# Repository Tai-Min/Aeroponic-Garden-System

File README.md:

# Thingy:53 Aeroponic Garden
2nd place in [Smarter Sustainable World Challenge
with Nordic Semiconductor](https://www.hackster.io/contests/smarter-sustainable-world). For details of the project itself see [Vertical Self Regulating Soilless Farm](https://www.hackster.io/Tai-Min/vertical-self-regulating-soilless-farm-a86d25)

## Physical setup
### The pot
* Print heater_bottom_n.stl and heater_top_n.stl (n = 1, 2, 3, 4) and glue them together. Insert 12V 5050 fan into place
* Print funnel.stl and insert it into heater glued in previous step
* Print num_layers * 4 layer_quarter.stl and glue them together then stack the layers and place them on top of the heater
* Print num_layers nozzle_frame.stl and num_layers * 4 nozzle_single.stl and glue them together then using straight plastic pipe assemble them starting from funnel's center intlet so that each nozzle_frame is on the level of the pot of given layer  
* Print nozzle_frame_end.stl and insert it at the top of previously created piping
* Print top_hat.stl and insert it at the top of vertical pot then insert Thingy:53 into it 
* Create wooden frame as in the pictures below
* Print valve_holder.stl and screw it at the bottom of the wooden quadropod then screw 12V valves into places
* Print num_layers * 4 - 1 of water_nozzle_frame.stl and nozzle_single.stl and glue them together then screw them on wooden structure so that each nozzle faces one pot
* Print 1 water_nozzle_frame_end.stl and single_nozzle.stl and glue them together and screw it on the wooden structure so it faces one pot
* Install LED strips on wooden structure so each pot has it's own light source

### RPi water system
* Print 2 pipe_holder_1.stl and pipe_holder_2.stl and glue them together on the side of both liquid tanks
* Print 2 pump_holder.stl and glue it at the bottom of the tank then screw the 12V pump into it
* Print 2 water_level_holder.stl, place it on the lids of both liquid tanks and then snap an ultrasonic sensor into them
* Screw reed switches into both liquid tanks and corresponding magnets into lids
* On nutrition water tank mount PCBs for EC and pH sensors and place the sensors into the tank itself

### Putting it together
Use flexible piping to connect the pot to water system as in the block diagram below:

## Electronics
Refer to KiCad project in /pi_shield folder for BOM and assembly purposes of the hats.

### The pot
Connect sensors / actuators to Thingy:53 control hat as in the block diagram below:

### RPi water system
Connect sensors / actuators to RPi's control hat as in the block diagram below:

## Attiny85
* Connect some programmer (i.e. ArduinoISP or USBasp) to Attiny85
* In platformio.ini change upload_protocol to your programmer
* You might also want to fine tune PH_MAGIC_NUMBER, TDS_A, TDS_B variables to match your sensor's characteristics
* In PlatformIO menu press "Set Fuses" in "attiny85" configuration, then click "Upload"
* Insert Attiny85 into Farm Overseers's shield

## Farm Overseer setup
* Setup Ubuntu Server 20.04 (i.e via [Raspberry Pi Imager](https://www.raspberrypi.com/software/))

### Enable UART
* Disable serial console
```
sudo systemctl stop serial-getty@ttyS0.service
sudo systemctl disable serial-getty@ttyS0.service
sudo systemctl mask serial-getty@ttyS0.service
```
* Put below into /etc/udev/rules.d/10-local.rules
```
KERNEL=="ttyS0", SYMLINK+="serial0" GROUP="tty" MODE="0660"
KERNEL=="ttyAMA0", SYMLINK+="serial1" GROUP="tty" MODE="0660"
```
* Reload udev rules
```
sudo udevadm control --reload-rules && sudo udevadm trigger
```
* Add user to tty (edit parts in "<>")
```
sudo adduser <USER> tty
```
* Delete below from /boot/firmware/cmdline.txt
```
console=serial0,115200
```
* Add below to /boot/firmware/config.txt
```
dtoverlay=disable-bt
```
### Enable 1-Wire
* Add below to /boot/firmware/config.txt
```
dtoverlay=w1-gpio,gpiopin=4
```

### ROS2
* Install [ROS2 Foxy Base version](https://docs.ros.org/en/foxy/Installation/Ubuntu-Install-Debians.html)
* Clone this repo to your home directory (/home/$USER/TODO)
* Build ROS components:
```bash
cd ~/TODO/ros_workspace && colcon build
```
* Place ROS setups in your .bashrc (edit parts in "<>")
```
source /opt/ros/foxy/setup.bash
source /home/<USER>/TODO/ros_workspace/install/setup.bash

```
### Mosquitto
* Install mosquitto 2.0
```
sudo add-apt-repository -y ppa:mosquitto-dev/mosquitto-ppa
sudo apt install mosquitto
sudo systemctl enable mosquitto
```

### zigbee2mqtt
* Install [zigbee2mqtt](https://www.zigbee2mqtt.io/guide/installation/01_linux.html) and set it to start as a daemon on boot. Use following config (edit parts in "<>"):
```yaml
mqtt:
  base_topic: field
  server: 'mqtt://localhost'

serial:
  port: <YOUR ZIGBEE DONGLE PORT>

advanced:
    network_key: GENERATE

external_converters:
  - fc.js
```

Create file /opt/zigbee2mqtt/data/fc.js and paste following into it:
```js
const fz = require('zigbee-herdsman-converters/converters/fromZigbee');
const tz = require('zigbee-herdsman-converters/converters/toZigbee');
const exposes = require('zigbee-herdsman-converters/lib/exposes');
const reporting = require('zigbee-herdsman-converters/lib/reporting');

const definition = {
    zigbeeModel: ['FC_v0.1'],
    model: 'FC',
    vendor: 'Nordic',
    description: 'Field Controller',
    fromZigbee: [fz.temperature, fz.humidity, fz.pressure, fz.on_off, fz.level_config],
    toZigbee: [tz.on_off, tz.level_config],
    exposes: [],
    configure: async (device, coordinatorEndpoint, logger) => {
        await reporting.bind(device.getEndpoint(16), coordinatorEndpoint, ['msTemperatureMeasurement']);
        await reporting.temperature(device.getEndpoint(16), { min: 30, max: 30, change: 0 });

        await reporting.bind(device.getEndpoint(16), coordinatorEndpoint, ['msPressureMeasurement']);
        await reporting.pressure(device.getEndpoint(16), { min: 30, max: 30, change: 0 });

        await reporting.bind(device.getEndpoint(16), coordinatorEndpoint, ['msRelativeHumidity']);
        await reporting.humidity(device.getEndpoint(16), { min: 30, max: 30, change: 0 });
    },
    endpoint: (device) => {
        return { fan: 10, led1: 11, led2: 12, strat: 13, water_valve: 14, nutri_valve: 15, sensors: 16 };
    },
};

module.exports = definition;
```

### Finishing up
* Reboot the board
```
sudo reboot now
```

## Field controller setup
Open field_controller/ in VSCode with nRF Connect and with Thingy:53 connected via JLink press flash.

## Run Farm Overseer's control algorithms
SSH into the Farm Overseer and run:
```
ros2 launch garden_meta system.launch.py
```

## Pair field controller to Farm Overseer
With Field Controller running cd into scripts/ and run:
```
./pair.sh -t 300
``` 
This will enable pairing for 300 seconds and should pair with the Field Controller.

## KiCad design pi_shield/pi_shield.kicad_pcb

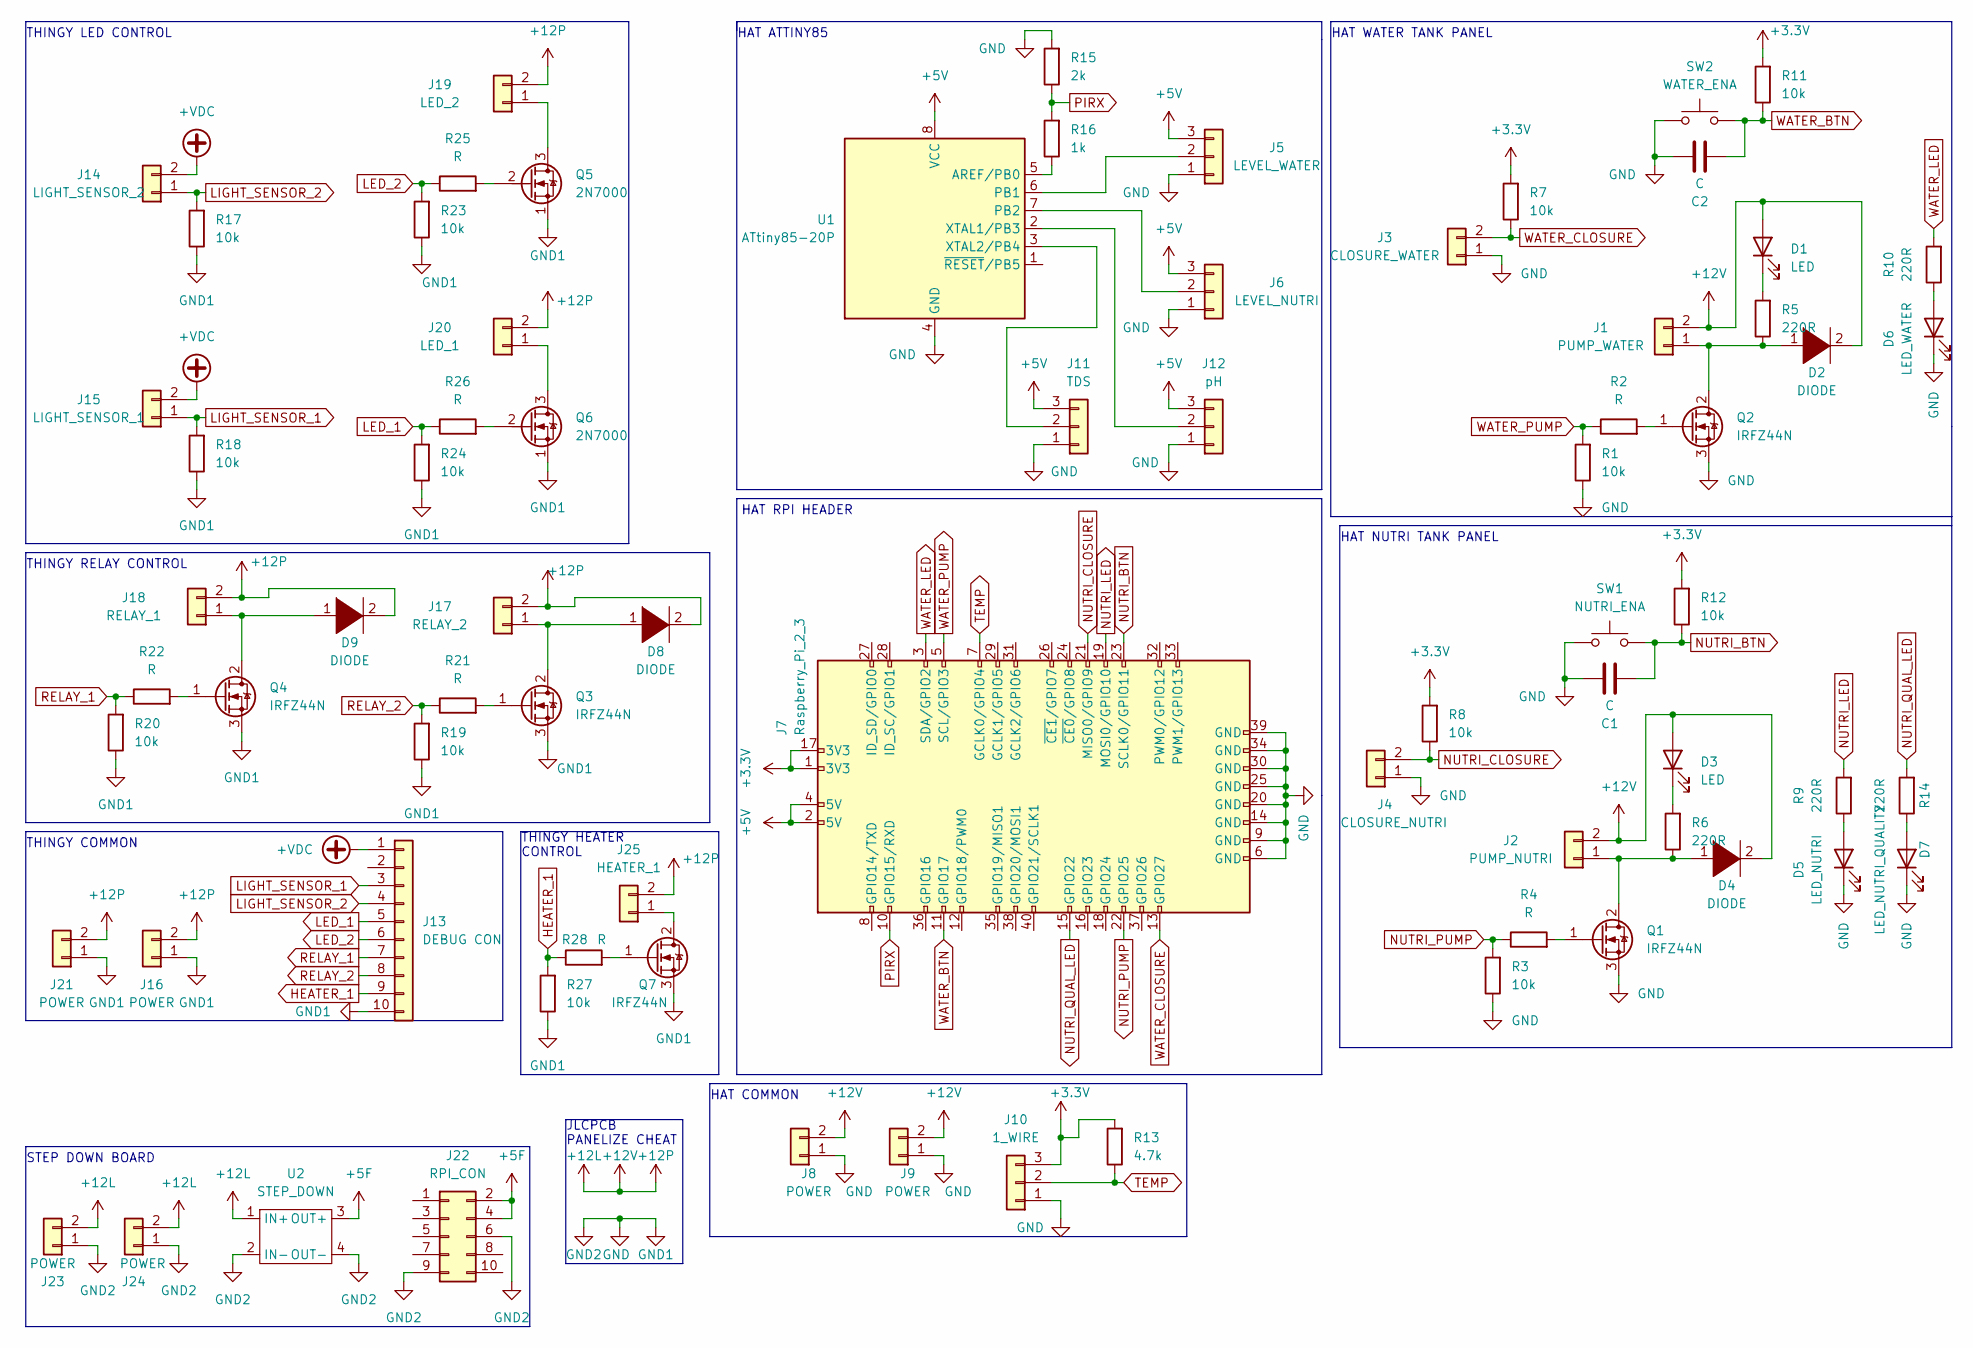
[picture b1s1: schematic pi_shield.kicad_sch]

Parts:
C1, C2: C; C_Disc_D5.0mm_W2.5mm_P2.50mm
D1, D3: LED; LED_D5.0mm_Clear
D2: DIODE; D_DO-15_P2.54mm_Vertical_AnodeUp
D4, D8, D9: DIODE; D_A-405_P2.54mm_Vertical_AnodeUp
D5: LED_NUTRI; LED_D5.0mm_Clear
D6: LED_WATER; LED_D5.0mm_Clear
D7: LED_NUTRI_QUALITY; LED_D5.0mm_Clear
J1: PUMP_WATER; Molex_SL_171971-0002_1x02_P2.54mm_Vertical
J2: PUMP_NUTRI; Molex_SL_171971-0002_1x02_P2.54mm_Vertical
J3: CLOSURE_WATER; Molex_SL_171971-0002_1x02_P2.54mm_Vertical
J4: CLOSURE_NUTRI; Molex_SL_171971-0002_1x02_P2.54mm_Vertical
J5: LEVEL_WATER; Molex_SL_171971-0003_1x03_P2.54mm_Vertical
J6: LEVEL_NUTRI; Molex_SL_171971-0003_1x03_P2.54mm_Vertical
J7: Raspberry_Pi_2_3; raspberrypi_2_3
J8, J9, J16, J21, J23, J24: POWER; Molex_SL_171971-0002_1x02_P2.54mm_Vertical
J10: 1_WIRE; Molex_SL_171971-0003_1x03_P2.54mm_Vertical
J11: TDS; Molex_SL_171971-0003_1x03_P2.54mm_Vertical
J12: pH; Molex_SL_171971-0003_1x03_P2.54mm_Vertical
J13: DEBUG CON; PinSocket_1x10_P2.54mm_Vertical
J14: LIGHT_SENSOR_2; Molex_SL_171971-0002_1x02_P2.54mm_Vertical
J15: LIGHT_SENSOR_1; Molex_SL_171971-0002_1x02_P2.54mm_Vertical
J17: RELAY_2; Molex_SL_171971-0002_1x02_P2.54mm_Vertical
J18: RELAY_1; Molex_SL_171971-0002_1x02_P2.54mm_Vertical
J19: LED_2; Molex_SL_171971-0002_1x02_P2.54mm_Vertical
J20: LED_1; Molex_SL_171971-0002_1x02_P2.54mm_Vertical
J22: RPI_CON; PinSocket_2x05_P2.54mm_Vertical
J25: HEATER_1; Molex_SL_171971-0002_1x02_P2.54mm_Vertical
Q1, Q2, Q7: IRFZ44N; TO-220-3_Horizontal_TabDown
Q3, Q4: IRFZ44N; TO-220-3_Vertical
Q5, Q6: 2N7000; TO-92L_Inline
R1, R3, R7, R8, R11, R12, R17, R18, R19, R20, R23, R24, R27: 10k; R_Axial_DIN0204_L3.6mm_D1.6mm_P2.54mm_Vertical
R2, R4, R21, R22, R25, R26, R28: R; R_Axial_DIN0204_L3.6mm_D1.6mm_P2.54mm_Vertical
R5, R6, R9, R10, R14: 220R; R_Axial_DIN0204_L3.6mm_D1.6mm_P2.54mm_Vertical
R13: 4.7k; R_Axial_DIN0204_L3.6mm_D1.6mm_P2.54mm_Vertical
R15: 2k; R_Axial_DIN0204_L3.6mm_D1.6mm_P2.54mm_Vertical
R16: 1k; R_Axial_DIN0204_L3.6mm_D1.6mm_P2.54mm_Vertical
SW1: NUTRI_ENA; SW_PUSH_6mm
SW2: WATER_ENA; SW_PUSH_6mm
U1: ATtiny85-20P; DIP-8_W7.62mm
U2: STEP_DOWN; SRT_MPT1584EN_Module

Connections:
+3.3V: J7.1 (3V3), J7.17 (3V3), J10.3, R7.2, R8.2, R11.2, R12.2, R13.2
+5F: J22.2, J22.4, U2.3 (OUT+)
+5V: J5.3, J6.3, J7.2 (5V), J7.4 (5V), J11.3, J12.3, U1.8 (VCC)
+12L: D1.2 (A), D2.2 (A), D3.2 (A), D4.2 (A), D8.2 (A), D9.2 (A), J1.2, J2.2, J8.2, J9.2, J16.2, J17.2, J18.2, J19.2, J20.2, J21.2, J23.2, J24.2, J25.2, U2.1 (IN+)
+VDC: J13.1, J14.2, J15.2
GND: C1.1, C2.1, D5.1 (K), D6.1 (K), D7.1 (K), J3.1, J4.1, J5.1, J6.1, J7.6 (GND), J7.9 (GND), J7.14 (GND), J7.20 (GND), J7.25 (GND), J7.30 (GND), J7.34 (GND), J7.39 (GND), J8.1, J9.1, J10.1, J11.1, J12.1, J13.10, J16.1, J21.1, J22.6, J22.9, J23.1, J24.1, Q1.3 (S), Q2.3 (S), Q3.3 (S), Q4.3 (S), Q5.1 (S), Q6.1 (S), Q7.3 (S), R1.1, R3.1, R15.2, R17.1, R18.1, R19.1, R20.1, R23.1, R24.1, R27.1, SW1.1, SW2.1, U1.4 (GND), U2.2 (IN-), U2.4 (OUT-)
HEATER_1: J13.9, R27.2, R28.1
LED_1: J13.5, R24.2, R26.1
LED_2: J13.6, R23.2, R25.1
LIGHT_SENSOR_1: J13.3, J15.1, R18.2
LIGHT_SENSOR_2: J13.4, J14.1, R17.2
NUTRI_BTN: C1.2, J7.23 (SCLK0/GPIO11), R12.1, SW1.2
NUTRI_CLOSURE: J4.2, J7.21 (MISO0/GPIO9), R8.1
NUTRI_LED: J7.19 (MOSI0/GPIO10), R9.2
NUTRI_PUMP: J7.22 (GPIO25), R3.2, R4.1
NUTRI_QUAL_LED: J7.15 (GPIO22), R14.2
unnamed: D1.1 (K), R5.2
unnamed: D2.1 (K), J1.1, Q2.2 (D), R5.1
unnamed: D3.1 (K), R6.2
unnamed: D4.1 (K), J2.1, Q1.2 (D), R6.1
unnamed: D5.2 (A), R9.1
unnamed: D6.2 (A), R10.1
unnamed: D7.2 (A), R14.1
unnamed: D8.1 (K), J17.1, Q3.2 (D)
unnamed: D9.1 (K), J18.1, Q4.2 (D)
unnamed: J5.2, U1.6 (PB1)
unnamed: J6.2, U1.7 (PB2)
unnamed: J11.2, U1.3 (XTAL2/PB4)
unnamed: J12.2, U1.2 (XTAL1/PB3)
unnamed: J19.1, Q5.3 (D)
unnamed: J20.1, Q6.3 (D)
unnamed: J25.1, Q7.2 (D)
unnamed: Q1.1 (G), R4.2
unnamed: Q2.1 (G), R2.2
unnamed: Q3.1 (G), R21.2
unnamed: Q4.1 (G), R22.2
unnamed: Q5.2 (G), R25.2
unnamed: Q6.2 (G), R26.2
unnamed: Q7.1 (G), R28.2
unnamed: R16.1, U1.5 (AREF/PB0)
PIRX: J7.10 (GPIO15/RXD), R15.1, R16.2
RELAY_1: J13.7, R20.2, R22.1
RELAY_2: J13.8, R19.2, R21.1
TEMP: J7.7 (GCLK0/GPIO4), J10.2, R13.1
WATER_BTN: C2.2, J7.11 (GPIO17), R11.1, SW2.2
WATER_CLOSURE: J3.2, J7.13 (GPIO27), R7.1
WATER_LED: J7.3 (SDA/GPIO2), R10.2
WATER_PUMP: J7.5 (SCL/GPIO3), R1.2, R2.1

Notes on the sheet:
HAT WATER TANK PANEL
THINGY COMMON
HAT NUTRI TANK PANEL
THINGY RELAY CONTROL
HAT RPI HEADER
HAT COMMON
STEP DOWN BOARD
HAT ATTINY85
THINGY HEATER CONTROL
JLCPCB PANELIZE CHEAT
THINGY LED CONTROL

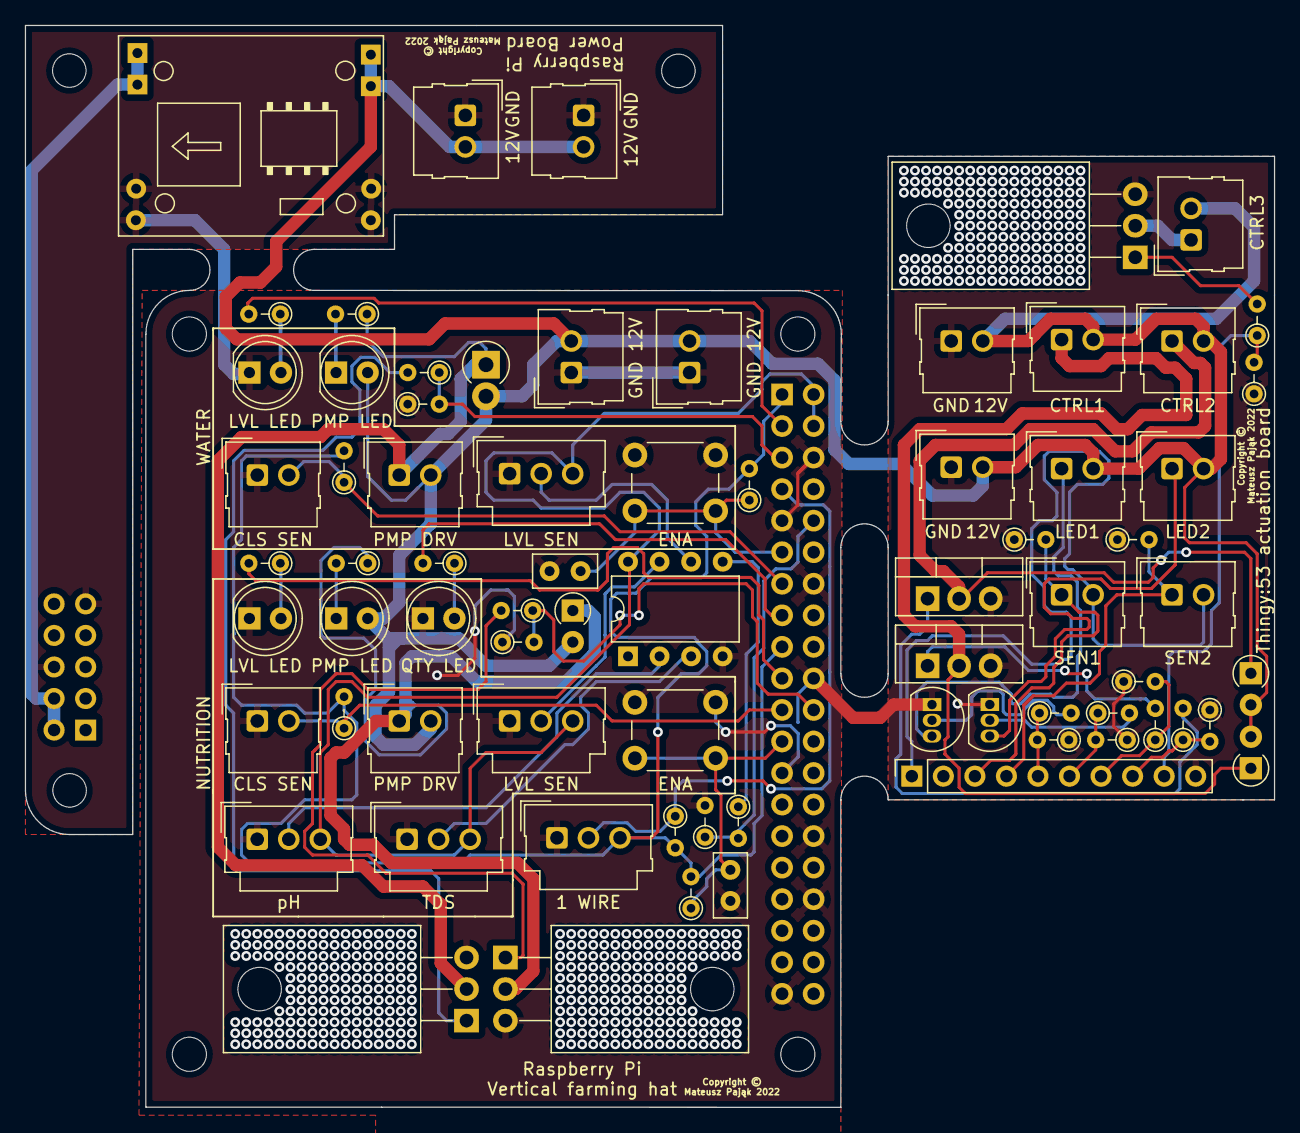
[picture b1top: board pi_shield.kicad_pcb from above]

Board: 2 copper layers, 100.6 x 87.1 mm, 75 parts (1 on the bottom side), 48 nets.

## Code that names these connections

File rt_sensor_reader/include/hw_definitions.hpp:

#pragma once
#include <stdint.h>
#include <avr/io.h>

constexpr uint8_t serial = PB0;

constexpr char u0Prefix[] = "u0";
constexpr uint8_t u0 = PB1;

constexpr char u1Prefix[] = "u1";
constexpr uint8_t u1 = PB2;

constexpr char phPrefix[] = "ph";
constexpr uint8_t ph = PB3;

constexpr char ecPrefix[] = "tds";
constexpr uint8_t ec = PB4;

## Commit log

2022-08-25 Add launch file
2022-08-26 Add garden control pkg, change variables in python nodes to private, edit config and system launch
2022-08-26 Add RT reader source code
2022-08-26 Add pi shield design files
2022-08-26 Add zigbee bridge
2022-08-29 Finish PCBs
2022-08-29 Add field controller folder
2022-08-29 Fix controller folder
2022-09-12 Edit field controller
2022-09-17 Bug fixes
2022-09-20 Modify field_controller, stamp rt_sensor_reader before remove Arduino UNO debug code
2022-09-20 Finish rt_sensor_reader
2022-09-20 Add delay to startup of rt_sensor_reader to not conflict with RPi boot
2022-09-20 Minor fixes
2022-09-22 Tune tds and ph sensors
2022-09-22 Add platformio.ini build flags for tds and ec sensors
2022-09-26 Replace EC with TDS in uc_bridge
2022-09-26 Add quality level observer
2022-09-26 Fix naming in submodules/common
2022-09-26 Add temperature observer
2022-09-27 Add temperature measurement
2022-09-27 Make Field Controller compile for once
2022-09-28 Make Field Controller upload to the device
2022-09-30 Resolve bug with field controller not starting w/ zigbee stack enabled
2022-10-09 Add zigbee bridge node
2022-10-09 Fix some bugs for zigbee bridge
2022-10-09 Add garden frontend
2022-10-10 Add functionality to Field Controller
2022-10-10 Finish frontend, add state publisher to pump driver
2022-10-10 Add garden meta package, fix some bugs
2022-10-10 Remove namespace from frontends
2022-10-23 Add neural classifier
2022-10-24 Add STL files
2022-10-24 Update diagram
2022-10-24 Add garden controller
2022-10-24 Bug fixes and param fixes
2022-10-24 Create LICENSE
2024-11-14 Update LICENSE

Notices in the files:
pi_shield/pi_shield.kicad_pcb:
Copyright ©
